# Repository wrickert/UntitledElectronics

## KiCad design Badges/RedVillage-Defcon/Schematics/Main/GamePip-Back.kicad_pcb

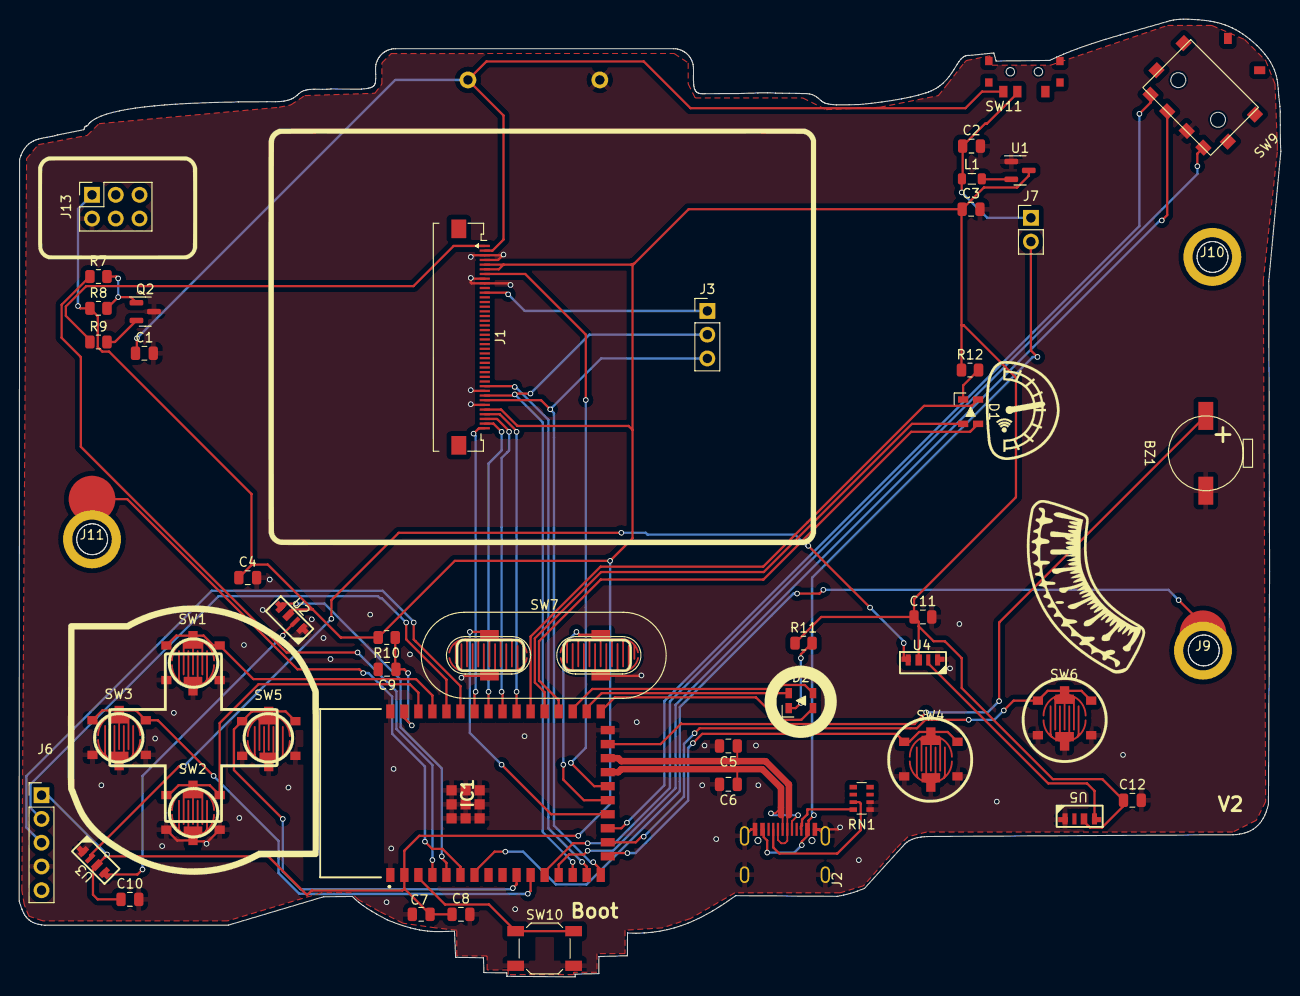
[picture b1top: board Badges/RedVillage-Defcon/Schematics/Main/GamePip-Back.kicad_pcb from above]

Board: 2 copper layers, 134.9 x 102.4 mm, 52 parts (1 on the bottom side), 53 nets.

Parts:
BT1: Battery; AA_TH
BZ1: Buzzer; FUET-9032-Buzzer
C1: 1uF; C_0805_2012Metric
C2: 10uF; C_0805_2012Metric
C3, C7: 22uF; C_0805_2012Metric
C4, C8, C9, C10, C11, C12: 100nF; C_0805_2012Metric
C5, C6: 20pF; C_0805_2012Metric
D1, D2: LED_RGBA; XL-3227RGB_LED
IC1: ESP32-S2-WROOM-I_M22S2H3200US3Q0_; ESP32S2WROOMIM22S2H3200US3Q0
J1: 2.8" Display; Omron_XF2M-4015-1A_1x40-1MP_P0.5mm_Horizontal
J2: USB_C_Plug_USB2.0; USB_C_Receptical-Jing
J3: Conn_01x03; PinHeader_1x03_P2.54mm_Vertical
J4, J5: Cap Sense; CapSense
J6: Conn_01x05; PinHeader_1x05_P2.54mm_Vertical
J7: Conn_01x02; PinHeader_1x02_P2.54mm_Vertical
J9, J10, J11: Conn_01x01; Threaded_Standoffs
J13: Conn_02x03_Odd_Even; PinSocket_2x03_P2.54mm_Vertical
L1: 10uH; L_0805_2012Metric
Q2: Q_NPN_BCE; SOT-23
R7, R10: 1k; R_0805_2012Metric
R8: 10k; R_0805_2012Metric
R9: 10R; R_0805_2012Metric
R11, R12: R_Small; R_0805_2012Metric
RN1: 5.1k; R_Array_Convex_4x0603
SW1: Up; BZCN-TSC005A_Button
SW2: Down; BZCN-TSC005A_Button
SW3: Left; BZCN-TSC005A_Button
SW4: A; BZCN-TSC005A_Button
SW5: Right; BZCN-TSC005A_Button
SW6: B; BZCN-TSC005A_Button
SW7: Start/Sel; StartSel
SW9: RotaryEncoder_Switch; SIQ-02FVS3_Encoder
SW10: Boot; SW_SPST_SKQG_WithoutStem
SW11: SW_SPDT; SK-3296S_switch
U1: SOT-23
U2, U3, U4, U5: SK6812_Side

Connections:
+5V: J2.A4 (VBUS), J2.A9 (VBUS), J2.B4 (VBUS), J2.B9 (VBUS), J7.2
/D+: C6.1, IC1.23 (IO20), J2.A6 (D+), J2.B6 (D+)
/D-: C5.1, IC1.24 (IO21), J2.A7 (D-), J2.B7 (D-)
/SK6812: IC1.5 (IO2), U2.1 (Din)
A: BT1.1 (+), C1.1, J1.2, SW11.1 (A)
A_Btn: IC1.17 (IO14), SW4.1
B: IC1.18 (IO15), SW6.1
B1: D2.4 (BK), IC1.27 (IO33)
B2: D1.4 (BK), IC1.31 (IO37)
BL: IC1.4 (IO1), R7.1
Boot: IC1.3 (IO0), SW10.1
Buzzer: BZ1.1 (-), IC1.25 (IO26)
DE: J1.11, J3.1
Disp_RESET: IC1.22 (IO19), J1.7
Down: IC1.40 (IO46), SW2.1
EnButton: IC1.13 (IO10), SW9.S
EnDown: IC1.12 (IO9), SW9.B
EnUp: IC1.19 (IO16), SW9.A
G1: D2.2 (GK), IC1.29 (IO35)
G2: D1.2 (GK), IC1.30 (IO36)
K: J1.1, R9.1
Left: IC1.11 (IO8), SW3.1
unnamed: D1.3 (A), R12.2
unnamed: D2.3 (A), R11.2
unnamed: IC1.6 (IO3), J4.1
unnamed: IC1.7 (IO4), J5.1
unnamed: J2.A5 (CC1), RN1.7 (R2.2)
unnamed: J2.B5 (CC2), RN1.8 (R1.2)
unnamed: Q2.1 (B), R7.2, R8.2
unnamed: Q2.2 (C), R9.2
unnamed: L1.2, U1.2 (LX)
unnamed: U2.3 (Dout), U3.1 (Din)
unnamed: U3.3 (Dout), U4.1 (Din)
unnamed: U4.3 (Dout), U5.1 (Din)
PwrTest: C2.1, J7.1, L1.1, SW11.2 (B)
R1: D2.1 (RK), IC1.28 (IO34)
R2: D1.1 (RK), IC1.32 (IO38)
RS: IC1.16 (IO13), J1.34, J3.3
RX: IC1.38 (RXD0), J6.2
Reset: C9.1, IC1.41 (EN), R10.1
Right: IC1.10 (IO7), SW5.1
SDA: IC1.15 (IO12), J1.31
Select: IC1.21 (IO18), SW7.3
Start: IC1.20 (IO17), SW7.1
TX: IC1.37 (TXD0), J6.3
Up: IC1.39 (IO45), SW1.1
VCC: C3.1, C4.1, C7.1, C8.1, C10.1, C11.1, C12.1, IC1.2 (3V3), J1.5, J1.6, J1.36, J6.1, J13.1, R8.1, R10.2, R11.1, R12.1, U1.3 (VOUT), U2.2 (VCC), U3.2 (VCC), U4.2 (VCC), U5.2 (VCC)
VSS: BT1.2 (-), BZ1.2 (+), C1.2, C2.2, C3.2, C4.2, C5.2, C6.2, C7.2, C8.2, C9.2, C10.2, C11.2, C12.2, IC1.1 (GND_1), IC1.26 (GND_2), IC1.42 (GND_3), IC1.43 (GND_4), IC1.44 (GND_5), IC1.45 (GND_6), IC1.46 (GND_7), IC1.47 (GND_8), IC1.48 (GND_9), IC1.49 (GND_10), IC1.50 (GND_11), IC1.51 (GND_12), J1.3, J1.4, J1.8, J1.9, J1.32, J1.35, J2.A1 (GND), J2.A12 (GND), J2.B1 (GND), J2.B12 (GND), J2.S1 (SHIELD), J6.4, J13.2, Q2.3 (E), RN1.1 (R1.1), RN1.2 (R2.1), SW1.2, SW2.2, SW3.2, SW4.2, SW5.2, SW6.2, SW7.2, SW9.C, SW10.2, U1.1 (VSS), U2.4 (GND), U3.4 (GND), U4.4 (GND), U5.4 (GND)
WR: IC1.14 (IO11), J1.33, J3.2
XL: IC1.35 (IO41), J1.39
XR: IC1.33 (IO39), J1.37
YD: IC1.34 (IO40), J1.38
YU: IC1.36 (IO42), J1.40

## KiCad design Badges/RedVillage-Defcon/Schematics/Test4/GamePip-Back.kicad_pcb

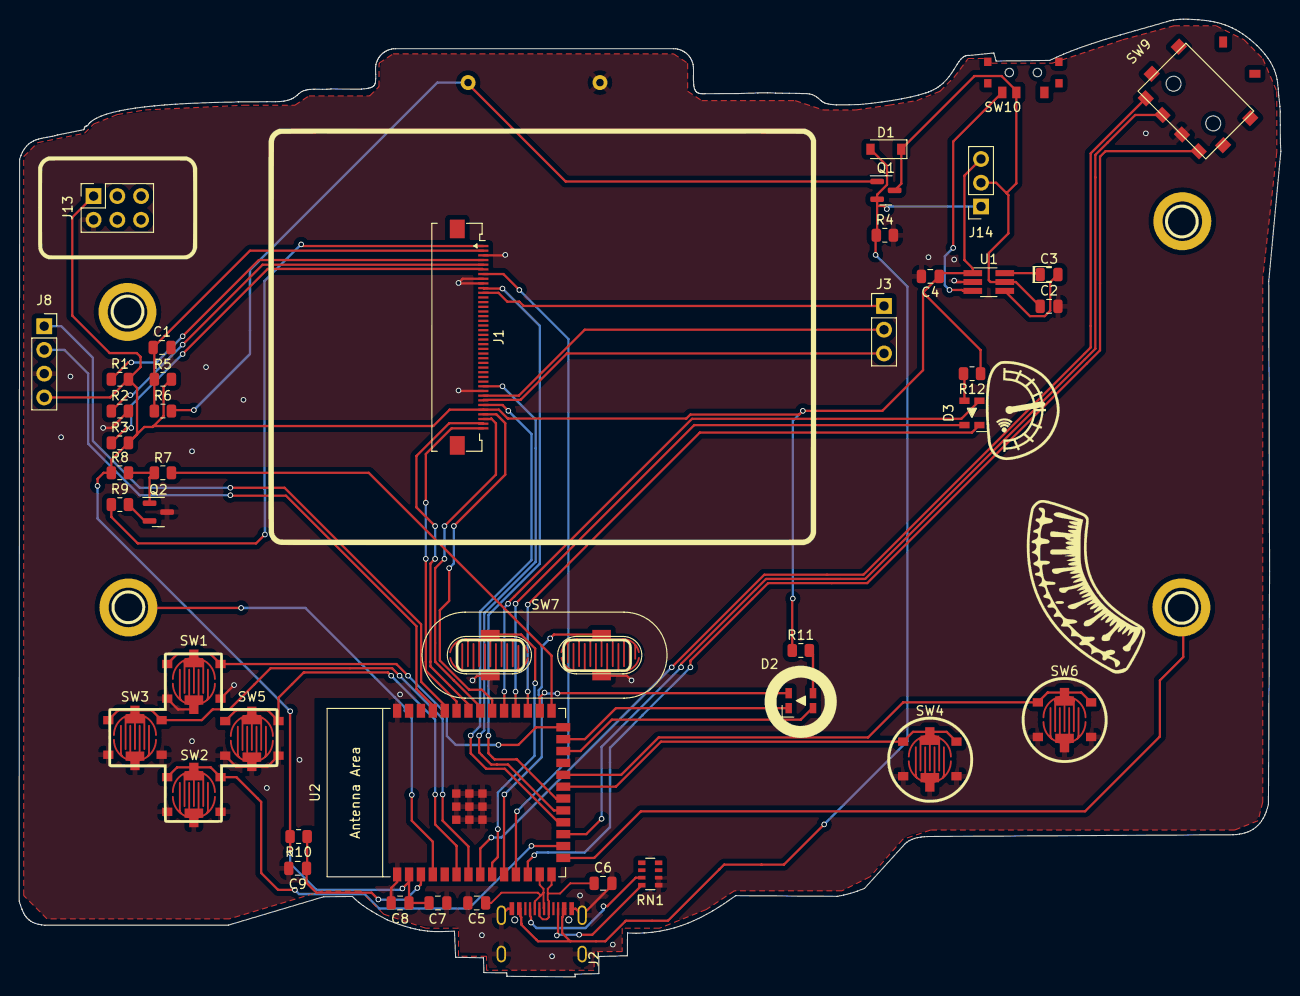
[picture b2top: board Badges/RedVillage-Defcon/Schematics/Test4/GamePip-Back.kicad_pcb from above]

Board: 2 copper layers, 134.9 x 102.4 mm, 51 parts (1 on the bottom side), 55 nets.

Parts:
BT1: Battery; AA_TH
C1: 1uF; C_0805_2012Metric
C2, C4: 10uF; C_0805_2012Metric
C3: 2.2uF; C_0805_2012Metric
C5, C6: 20pF; C_0805_2012Metric
C7: 22uF; C_0805_2012Metric
C8, C9: 100nF; C_0805_2012Metric
D1: D_Schottky; D_SOD-123
D2, D3: LED_RGBA; XL-3227RGB_LED
J1: 2.8" Display; Omron_XF2M-4015-1A_1x40-1MP_P0.5mm_Horizontal
J2: USB_C_Plug_USB2.0; USB_C_Receptical-Jing
J3: Conn_01x03; PinHeader_1x03_P2.54mm_Vertical
J5, J6: Cap Sense; CapSense
J8: Conn_01x04; PinSocket_1x04_P2.54mm_Vertical
J9, J10, J11, J12: Conn_01x01; SMD Spacer M2.5
J13: Conn_02x03_Odd_Even; PinSocket_2x03_P2.54mm_Vertical
J14: Conn_01x03; PinSocket_1x03_P2.54mm_Vertical
Q1: Q_PMOS_DGS; SOT-23
Q2: Q_NPN_BCE; SOT-23
R1, R3: Jumper; R_0805_2012Metric
R2, R11, R12: R_Small; R_0805_2012Metric
R4: 100k; R_0805_2012Metric
R5, R6: 0ohm; R_0805_2012Metric
R7, R10: 1k; R_0805_2012Metric
R8: 10k; R_0805_2012Metric
R9: 10R; R_0805_2012Metric
RN1: 5.1k; R_Array_Convex_4x0603
SW1: Up; BZCN-TSC005A_Button
SW2: Down; BZCN-TSC005A_Button
SW3: Left; BZCN-TSC005A_Button
SW4: A; BZCN-TSC005A_Button
SW5: Right; BZCN-TSC005A_Button
SW6: B; BZCN-TSC005A_Button
SW7: Start/Sel; StartSel
SW9: RotaryEncoder_Switch; SIQ-02FVS3_Encoder
SW10: Power; SK-3296S_switch
U1: XDS_TX4310B; TSOT-23-6_HandSoldering
U2: ESP32-S2-SOLO

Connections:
+5V: D1.2 (A), J2.A4 (VBUS), J2.A9 (VBUS), J2.B4 (VBUS), J2.B9 (VBUS), J14.1, Q1.2 (G), R4.1
/D+: C6.1, J2.A6 (D+), J2.B6 (D+), U2.14 (GPIO20/U1CTS/ADC2_CH9/CLK_OUT1/USB_D+)
/D-: C5.1, J2.A7 (D-), J2.B7 (D-), U2.13 (GPIO19/U1RTS/ADC2_CH8/CLK_OUT2/USB_D-)
A: C1.1, J1.2, R5.2, R6.1
A_Btn: SW4.1, U2.21 (GPIO13/TOUCH13/ADC2_CH2/FSPIQ/FSPIIO7)
B: SW6.1, U2.22 (GPIO14/TOUCH14/ADC2_CH3/FSPIWP/FSPIDQS)
B1: D2.3 (BK), U2.28 (SPIIO6/GPIO35/FSPID)
B2: D3.3 (BK), U2.30 (SPIDQS/GPIO37/FSPIQ)
BL: R7.1, U2.27 (GPIO0)
CS: J1.35, U2.18 (GPIO10/TOUCH10/ADC1_CH9/FSPICS0/FSPIIO4)
DE: J1.11, J3.1
Disp_RESET: J1.7, U2.11 (GPIO18/U1RXD/ADC2_CH7/DAC_2/CLK_OUT3)
Down: SW2.1, U2.16 (GPIO46)
EnButton: SW9.S, U2.17 (GPIO9/TOUCH9/ADC1_CH8/FSPIHD)
EnDown: SW9.B, U2.12 (GPIO8/TOUCH8/ADC1_CH7)
EnUp: SW9.A, U2.8 (GPIO15/U0RTS/ADC2_CH4/XTAL_32K_P)
G1: D2.2 (GK), U2.24 (SPIIO4/GPIO33/FSPIHD)
G2: D3.2 (GK), U2.31 (GPIO38/FSPIWP)
IM0: J1.4, R1.1
IM1: J1.5, R2.1
IM2: J1.6, R3.1
K: J1.1, R9.1
Left: SW3.1, U2.7 (GPIO7/TOUCH7/ADC1_CH6)
unnamed: C3.1, U1.6 (C+)
unnamed: C3.2, U1.4 (C-)
unnamed: D2.4 (A), R11.2
unnamed: D3.4 (A), R12.2
unnamed: J2.A5 (CC1), RN1.7 (R2.2)
unnamed: J2.B5 (CC2), RN1.8 (R1.2)
unnamed: J5.1, U2.15 (GPIO3/TOUCH3/ADC1_CH2)
unnamed: J6.1, U2.4 (GPIO4/TOUCH4/ADC1_CH3)
unnamed: Q2.1 (B), R7.2, R8.2
unnamed: Q2.2 (C), R9.2
unnamed: SW10.1 (A), U1.3 (En)
PCLK: J1.10, U2.20 (GPIO12/TOUCH12/ADC2_CH1/FSPICLK/FSPIIO6)
PreXDS: C2.1, D1.1 (K), J14.2, Q1.3 (S), SW10.2 (B), U1.5 (VDD)
R1: D2.1 (RK), U2.25 (SPIIO5/GPIO34/FSPICS0)
R2: D3.1 (RK), U2.29 (SPIIO7/GPIO36/FSPICLK)
RS: J1.34, J3.3
RX: J8.1, U2.36 (U0RXD/GPIO44/CLK_OUT2)
Reset: C9.1, R10.1, U2.3 (EN)
Right: SW5.1, U2.6 (GPIO6/TOUCH6/ADC1_CH5)
SDA: J1.31, U2.19 (GPIO11/TOUCH11/ADC2_CH0/FSPID/FSPIIO5)
Select: SW7.3, U2.10 (GPIO17/U1TXD/ADC2_CH6/DAC_1)
Start: SW7.1, U2.9 (GPIO16/U0CTS/ADC2_CH5/XTAL_32K_N)
TX: J8.2, U2.37 (U0TXD/GPIO43/CLK_OUT1)
Up: SW1.1, U2.26 (GPIO45)
VCC: C4.1, C7.1, C8.1, J1.36, J8.4, J13.1, J14.3, R1.2, R3.2, R5.1, R8.1, R10.2, R11.1, R12.1, U1.1 (Vout), U2.2 (3V3)
VDD: BT1.1 (+), Q1.1 (D), R6.2
VSS: BT1.2 (-), C1.2, C2.2, C4.2, C5.2, C6.2, C7.2, C8.2, C9.2, J1.3, J1.8, J1.9, J1.32, J2.A1 (GND), J2.A12 (GND), J2.B1 (GND), J2.B12 (GND), J2.S1 (SHIELD), J8.3, J13.2, Q2.3 (E), R2.2, R4.2, RN1.1 (R1.1), RN1.2 (R2.1), SW1.2, SW2.2, SW3.2, SW4.2, SW5.2, SW6.2, SW7.2, SW9.C, U1.2 (GND), U2.1 (GND), U2.40 (GND), U2.41 (GND)
WR: J1.33, J3.2
XL: J1.39, U2.34 (MTDI/GPIO41/CLK_OUT1)
XR: J1.37, U2.32 (MTCK/GPIO39/CLK_OUT3)
YD: J1.38, U2.33 (MTDO/GPIO40/CLK_OUT2)
YU: J1.40, U2.35 (MTMS/GPIO42)

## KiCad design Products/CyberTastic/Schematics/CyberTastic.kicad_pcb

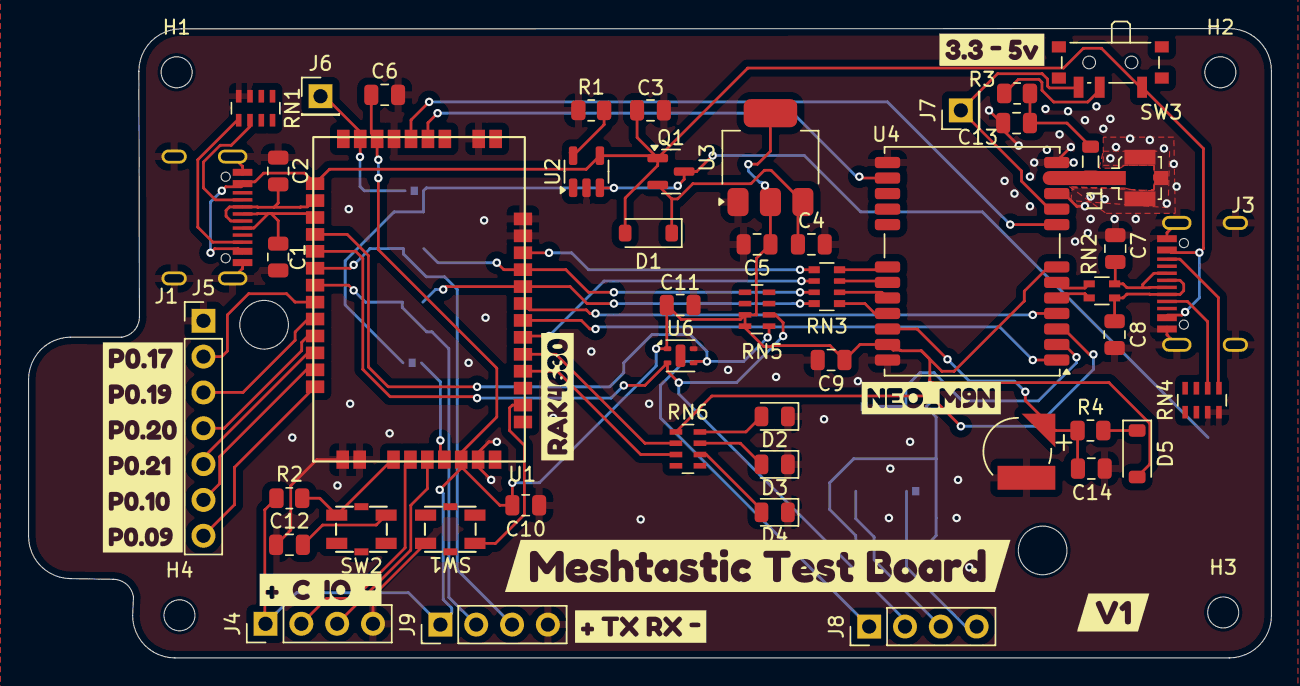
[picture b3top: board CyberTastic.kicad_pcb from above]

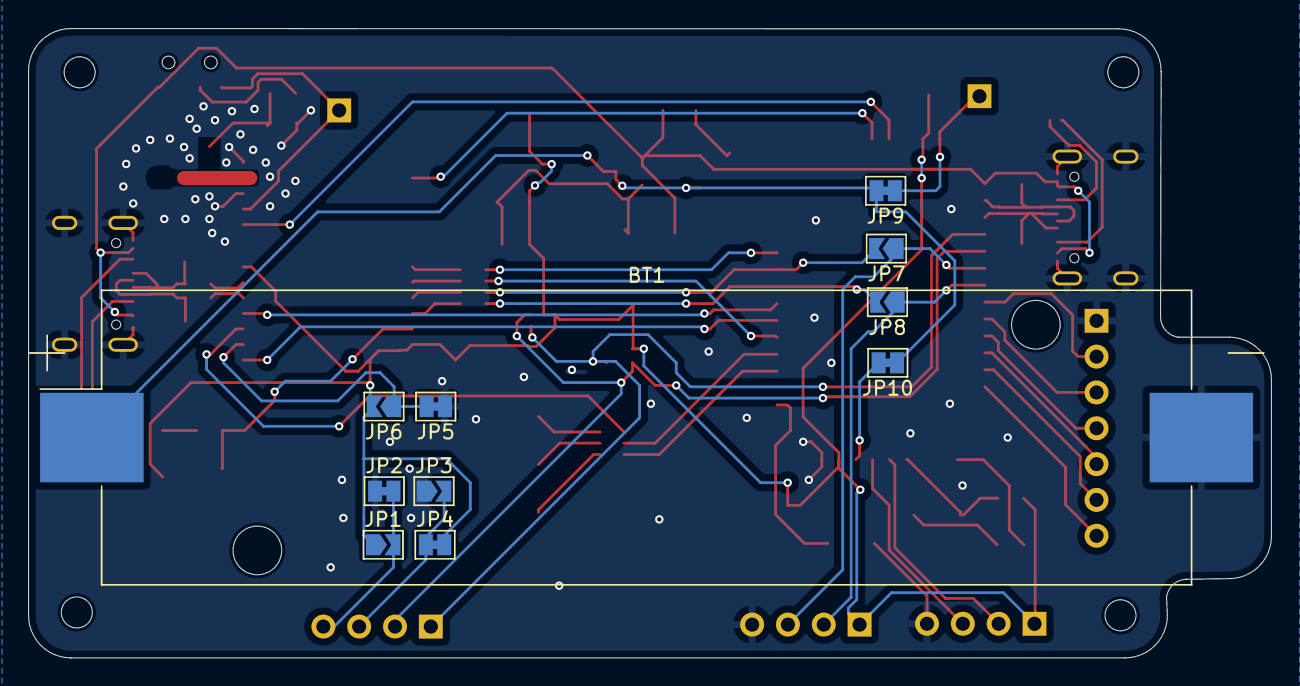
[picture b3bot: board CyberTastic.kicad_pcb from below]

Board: 2 copper layers, 88.1 x 44.6 mm, 72 parts (11 on the bottom side), 60 nets.

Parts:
BT1: Battery_Cell; BatteryHolder_Keystone_1042_1x18650
BT2: Battery_Cell; SEIKO_ML414H_IV01E
C1, C2, C7, C8: TBD; C_0805_2012Metric
C3: 22uF; C_0805_2012Metric
C4, C5: 10uF; C_0805_2012Metric
C6, C9, C10, C11, C12, C13, C14: 100nF; C_0805_2012Metric
D1, D5: D_Schottky; D_SOD-123
D2, D3, D4: LED_Small; LED_0805_2012Metric
H1, H2, H3, H4: MountingHole; MountingHole_2.2mm_M2
J1, J3: USB_C_Receptacle; USB_C_Receptical-Jing
J2: U.FL; U.FL_Molex_MCRF_73412-0110_Vertical
J4, J9: Conn_01x04; PinHeader_1x04_P2.54mm_Vertical
J5: Conn_01x07; PinHeader_1x07_P2.54mm_Vertical
J6: Bodge; PinHeader_1x01_P2.54mm_Vertical
J7: Conn_01x01; PinHeader_1x01_P2.54mm_Vertical
J8: OledDisplay; PinHeader_1x04_P2.54mm_Vertical
JP1: JOpen; SolderJumper-2_P1.3mm_Open_TrianglePad1.0x1.5mm
JP2: JClosed; SolderJumper-2_P1.3mm_Bridged_Pad1.0x1.5mm
JP3, JP6, JP7, JP8: Jumper_2_Open; SolderJumper-2_P1.3mm_Open_TrianglePad1.0x1.5mm
JP4, JP5, JP9, JP10: Jumper_2_Bridged; SolderJumper-2_P1.3mm_Bridged_Pad1.0x1.5mm
L1: 27nH; L_0805_2012Metric
Q1: AO3401A; SOT-23
R1: R_Small; R_0805_2012Metric
R2: 10k; R_0805_2012Metric
R3: 10; R_0805_2012Metric
R4: 1k; R_0805_2012Metric
RN1, RN4, RN5, RN6: 5.1k; R_Array_Concave_4x0603
RN2: 27; R_Array_Convex_2x0603
RN3: 33; R_Array_Convex_4x0603
SW1, SW2: SW_SPST; TS3315A
SW3: SW_SPDT; SW_SPDT_PCM12
U1: RAK4630
U2: LTC4054ES5; TSOT-23-5
U3: TLV1117-33; SOT-223-3_TabPin2
U4: NEO-M9N; ublox_NEO
U6: SHTC3; Sensirion_DFN-4-1EP_2x2mm_P1mm_EP0.7x1.6mm
kibuzzard-665A1BDF: G***; kibuzzard-665A1BDF
kibuzzard-665A1C19: G***; kibuzzard-665A1C19
kibuzzard-665A1C85: G***; kibuzzard-665A1C85
kibuzzard-665A1CA2: G***; kibuzzard-665A1CA2
kibuzzard-665A1CD2: G***; kibuzzard-665A1CD2
kibuzzard-665A1D5A: G***; kibuzzard-665A1D5A
kibuzzard-665A1D6B: G***; kibuzzard-665A1D6B
kibuzzard-665A1E07: G***; kibuzzard-665A1E07

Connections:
+5V: C3.2, D1.2 (A), J1.A4 (VBUS), J1.A9 (VBUS), J1.B4 (VBUS), J1.B9 (VBUS), J3.A4 (VBUS), J3.A9 (VBUS), J3.B4 (VBUS), J3.B9 (VBUS), Q1.1 (G), SW3.1 (A), U1.1 (VBus), U2.4 (V_{CC})
/D+: C1.1, J1.A6 (D+), J1.B6 (D+), U1.3 (D+)
/D-: C2.1, J1.A7 (D-), J1.B7 (D-), U1.2 (D-)
/RX/MOSI: JP8.2 (B), RN3.8 (R1.2), U1.32 (P0.29)
/SCL/CLK: RN3.6 (R3.2), U1.29 (P0.03)
/SDA/CS: RN3.5 (R4.2), U1.34 (P0.26)
/TX/MISO: JP7.2 (B), RN3.7 (R2.2), U1.33 (P0.30)
Batt: BT1.1 (+), JP9.2 (B), JP10.1 (A), Q1.3 (D), U2.3 (BAT)
Data_Sel: JP5.2 (B), JP6.1 (A), U4.2 (D_SEL)
EXTINT: U1.31 (P0.28), U4.4 (EXTINT)
GPS_D+: C7.1, J3.A6 (D+), J3.B6 (D+), RN2.4 (R1.2)
GPS_D-: C8.1, J3.A7 (D-), J3.B7 (D-), RN2.3 (R2.2)
LED1: RN6.3 (R3.1), U1.27 (P1.03)
LED2: RN6.2 (R2.1), U1.28 (P1.04)
LND_EN: U1.40 (P0.05), U4.14 (LNA_EN)
unnamed: BT2.1 (+), C14.1, R4.1, U4.22 (V_BCKP)
unnamed: C13.1, L1.2, R3.1
unnamed: C4.1, D1.1 (K), Q1.2 (S), U3.3 (VI)
unnamed: D2.2 (A), RN6.8 (R1.2)
unnamed: D3.2 (A), RN6.7 (R2.2)
unnamed: D4.2 (A), RN6.6 (R3.2)
unnamed: D5.1 (K), R4.2
unnamed: J1.A5 (CC1), RN1.6 (R3.2)
unnamed: J1.B5 (CC2), RN1.5 (R4.2)
unnamed: J2.1 (In), L1.1, U4.11 (RF_IN)
unnamed: J3.A5 (CC1), RN4.6 (R3.2)
unnamed: J3.B5 (CC2), RN4.5 (R4.2)
unnamed: J6.1, JP9.1 (A), U1.44 (VBAT_NRF)
unnamed: J7.1, SW3.3 (C), U4.9 (VCC_RF)
unnamed: J8.3, JP3.2 (B), JP4.1 (A)
unnamed: J8.4, JP1.2 (B), JP2.2 (B)
unnamed: JP10.2 (B), U1.20 (VBatt_SX)
unnamed: RN2.1 (R1.1), U4.6 (USB_DP)
unnamed: RN2.2 (R2.1), U4.5 (USB_DM)
unnamed: RN3.1 (R1.1), U4.21 (RXD/SPI_MOSI)
unnamed: RN3.2 (R2.1), U4.20 (TXD/SPI_MISO)
unnamed: RN3.3 (R3.1), U4.19 (SCL/SPI_CLK)
unnamed: RN3.4 (R4.1), U4.18 (SDA/~SPI_CS)
unnamed: SW1.1 (A), U1.25 (P1.01)
unnamed: R2.1, SW2.1 (A), U1.17 (Reset)
unnamed: C12.2, SW2.2 (B)
unnamed: R3.2, SW3.2 (B)
unnamed: R1.2, U2.5 (PROG)
P0.09: J5.7, U1.13 (P0.09)
P0.10: J5.6, U1.12 (P0.10)
P0.17: J5.2, U1.8 (P0.17)
P0.19: J5.3, U1.9 (P0.19)
P0.20: J5.4, U1.10 (P0.20)
P0.21: J5.5, U1.11 (P0.21)
RESET: U1.41 (P0.04), U4.8 (~RESET)
RX: J9.3, JP7.1 (A), U1.6 (P0.15)
SAFEBOOT: U1.30 (P0.02), U4.1 (~SAFEBOOT)
SCL: J8.2, RN5.6 (R3.2), U1.5 (P0.14), U6.2 (SCL)
SDA: J8.1, RN5.5 (R4.2), U1.4 (P0.13), U6.3 (SDA)
SWDCLK: J4.2, U1.18 (SWDCLK)
SWDIO: J4.3, U1.19 (SWDIO)
TX: J9.2, JP8.1 (A), U1.7 (P0.16)
Timepulse: RN6.1 (R1.1), U4.3 (TIMEPULSE)
VCC: C5.1, C6.1, C9.1, C10.2, C11.2, D5.2 (A), J4.1, J9.1, JP1.1 (A), JP4.2 (B), JP6.2 (B), R2.2, RN5.3 (R3.1), RN5.4 (R4.1), U1.21 (VBAT_IO_SX), U1.43 (VDD_NRF), U3.2 (VO), U4.7 (VDD_USB), U4.23 (VCC), U6.1 (VDD)
VSS: BT1.2 (-), BT2.2 (-), C1.2, C2.2, C3.1, C4.2, C5.2, C6.2, C7.2, C8.2, C9.2, C10.1, C11.1, C12.1, C13.2, C14.2, D2.1 (K), D3.1 (K), D4.1 (K), J1.A1 (GND), J1.A12 (GND), J1.B1 (GND), J1.B12 (GND), J1.S1 (SHIELD), J2.2 (Ext), J3.A1 (GND), J3.A12 (GND), J3.B1 (GND), J3.B12 (GND), J3.S1 (SHIELD), J4.4, J5.1, J9.4, JP2.1 (A), JP3.1 (A), JP5.1 (A), R1.1, RN1.3 (R3.1), RN1.4 (R4.1), RN4.3 (R3.1), RN4.4 (R4.1), SW1.2 (B), U1.14 (VSS), U1.16 (VSS), U1.22 (VSS), U1.35 (VSS), U1.36 (VSS), U1.38 (VSS), U1.42 (VSS), U2.2 (GND), U3.1 (GND), U4.10 (GND), U4.12 (GND), U4.13 (GND), U4.24 (GND), U6.4 (VSS)

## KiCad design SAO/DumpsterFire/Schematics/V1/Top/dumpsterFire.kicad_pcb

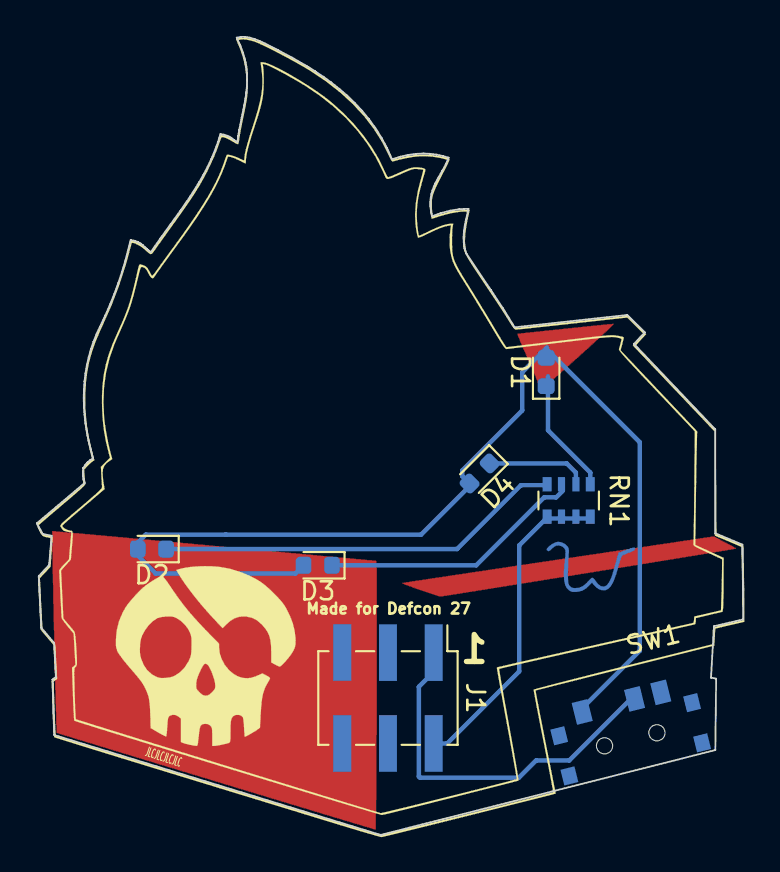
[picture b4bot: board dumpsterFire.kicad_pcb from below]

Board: 2 copper layers, 39.2 x 44.3 mm, 10 parts (9 on the bottom side), 7 nets.

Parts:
D1, D2, D3, D4: LED_Small; LED_0603_1608Metric
J1: Conn_02x03_Odd_Even; PinHeader_2x03_P2.54mm_Vertical_SMD
RN1: 330; R_Array_Convex_4x0603
Ref**: Val**; BPSkull
Ref**#2: Val**; W
Ref**#3: Val**; dumpsterFireMiddle
SW1: SW_SPDT; SK-3296S_switch

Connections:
+3V3: J1.1, SW1.2
unnamed: D1.1, RN1.1
unnamed: D2.1, RN1.4
unnamed: D3.1, RN1.3
unnamed: D4.1, RN1.2
VCC: D1.2, D2.2, D3.2, D4.2, SW1.3
VSS: J1.2, RN1.5, RN1.6, RN1.7, RN1.8
